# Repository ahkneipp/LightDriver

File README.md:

# LightDriver
Control system for a strip of WS2811 LEDs; Quick and dirty

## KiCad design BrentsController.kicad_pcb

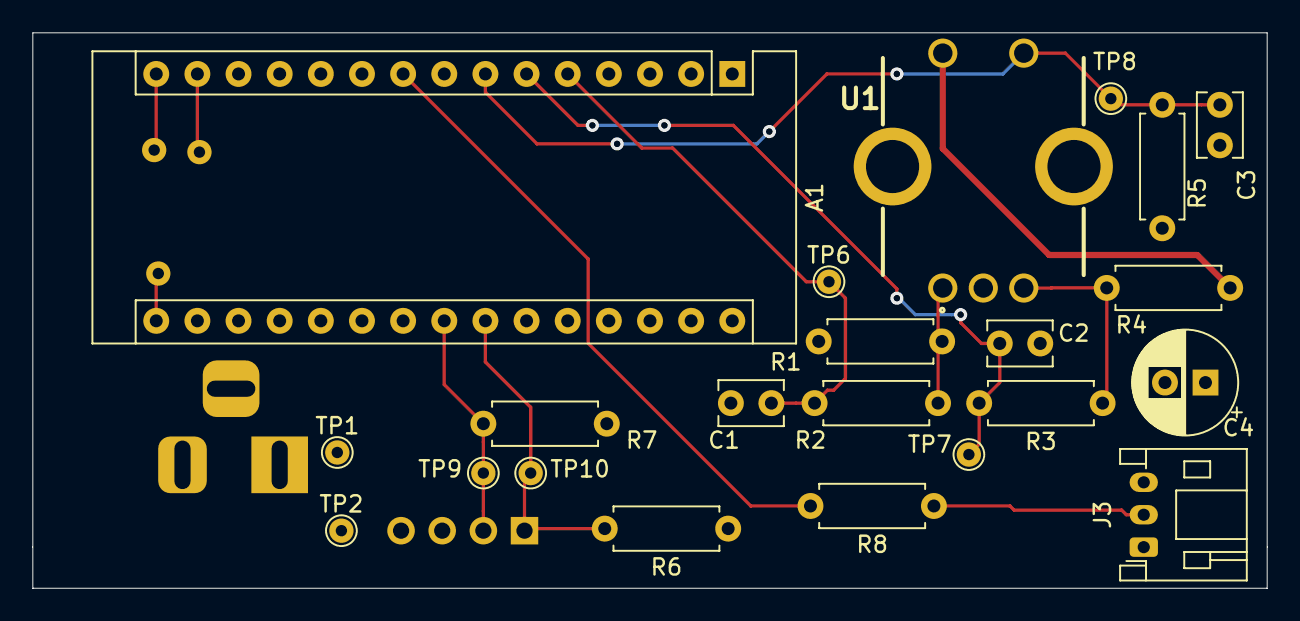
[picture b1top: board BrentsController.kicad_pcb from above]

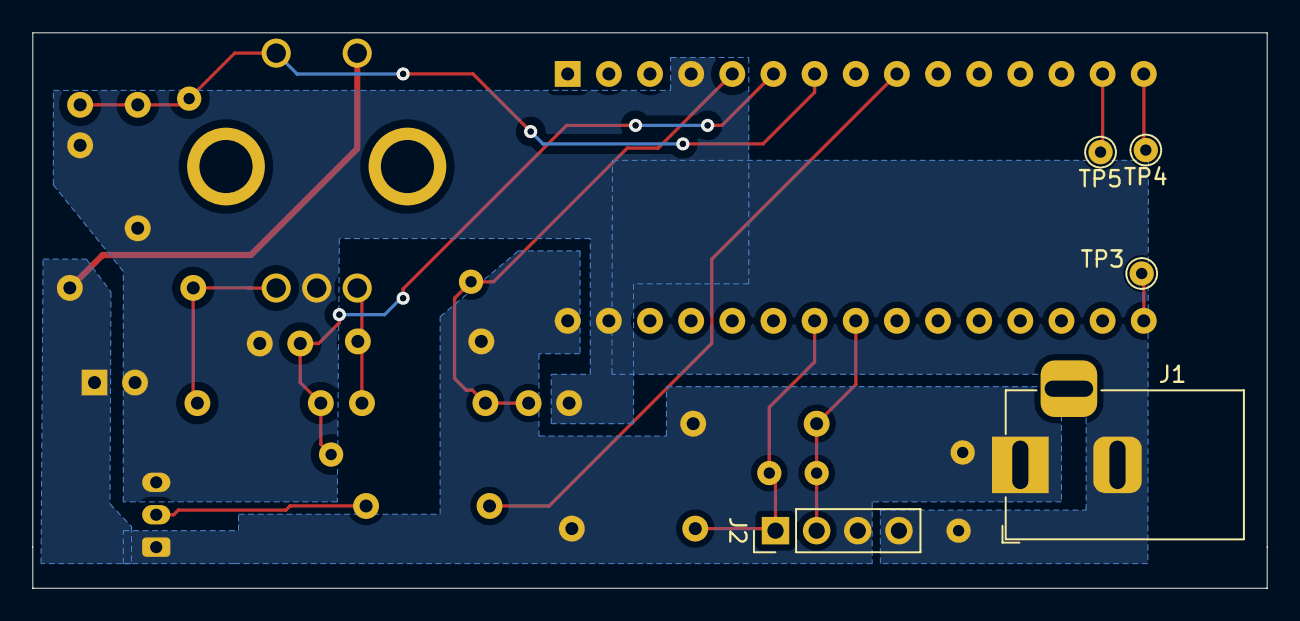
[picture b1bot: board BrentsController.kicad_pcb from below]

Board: 2 copper layers, 76.2 x 34.3 mm, 27 parts (5 on the bottom side), 14 nets.

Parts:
A1: Arduino_Nano_v3.x; Arduino_Nano
C1, C2: 10nF; C_Disc_D3.8mm_W2.6mm_P2.50mm
C3: 22nF; C_Disc_D3.8mm_W2.6mm_P2.50mm
C4: 330u; CP_Radial_D6.3mm_P2.50mm
J1: Barrel_Jack_Switch; BarrelJack_Horizontal
J2: Conn_01x04_Male; PinHeader_1x04_P2.54mm_Vertical
J3: Conn_01x03_Female; JST_PH_S3B-PH-K_1x03_P2.00mm_Horizontal
R1, R2, R3, R4, R5: 10k; R_Axial_DIN0207_L6.3mm_D2.5mm_P7.62mm_Horizontal
R6, R7: 4.7k; R_Axial_DIN0207_L6.3mm_D2.5mm_P7.62mm_Horizontal
R8: 330; R_Axial_DIN0207_L6.3mm_D2.5mm_P7.62mm_Horizontal
TP1, TP2, TP3, TP4, TP5, TP6, TP7, TP8, TP9, TP10: TestPoint; TestPoint_THTPad_D1.5mm_Drill0.7mm
U1: PEC12R-4225F-S0024; PEC12R-4XXXF-SXXXX_1

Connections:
/ENC_A: A1.5, C1.1, R2.2, TP6.1
/ENC_B: A1.6, C2.1, R3.2, TP7.1
/ENC_BTN: A1.7, C3.1, R5.1, TP8.1, U1.5
/I2C_SCL: A1.24, J2.1, R6.2, TP10.1
/I2C_SDA: A1.23, J2.2, R7.2, TP9.1
/LED_DATA: A1.9, R8.2
/TP_D11: A1.14, TP5.1
/TP_D12: A1.15, TP4.1
/TP_D13: A1.16, TP3.1
GNDD: A1.4, A1.29, C1.2, C2.2, C3.2, C4.2, J1.2, J2.4, J3.3, R5.2, TP2.1, U1.2
unnamed: J3.2, R8.1
unnamed: R1.1, R2.1, U1.1
unnamed: R3.1, R4.2, U1.3
VCC: A1.30, C4.1, J1.1, J2.3, J3.1, R1.2, R4.1, R6.1, R7.1, TP1.1, U1.4

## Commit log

2019-10-29 Adds to git tracking
2019-10-29 Add the code for the project to git tracking
2019-10-29 Fixes the encoder debouncing networks and uController pin connections
2019-10-31 Fixes some errors and adds ALL THE TESTPOINTS
2019-10-31 Adds netlist to gitignore
2019-10-31 Ignores Gerbers and zips
2019-10-31 Finishes the layout
2019-10-31 Generating Gerbers
2019-11-07 Generates BOM
2019-11-07 Adds basic menu state machine
2019-11-16 Adds additional state machine states and moves state machine to another function
2019-11-19 Documents the state machine states
2019-11-19 Started implementing missing states
2019-11-19 Adds util.hpp for structs and such
2019-11-19 Adds pattern to config struct
2019-11-19 Fixes compiler errors
2019-11-19 I missed a few compile errors
2019-11-19 Adds skeletons for the unimplemented states
2019-12-16 Found an LCD library which actually works
2019-12-22 Made a bunch of progress it would really suck to lose
2019-12-22 Missed the patterns code in the last commit
2019-12-22 Gets a fire pattern I'm more or less happy with
2019-12-22 Gets code in deployable state
